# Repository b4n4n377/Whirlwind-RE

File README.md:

# Whirlwind-RE
Clone / Reverse Engineering of the open source 'Whirlwind - PC to JAMMA Arcade Cabinet Interface'
- see https://www.instructables.com/Whirlwind-PC-to-JAMMA-Arcade-Cabinet-Interface/
- see https://github.com/baritonomarchetto/Whirlwind

We encountered a problem where too little voltage reached the video amp due to the voltage divider at pin 1 of the RPI2040 used for sync control.

To address this, we implemented a different sync circuit.

This is one of our very first designs. Ideas for further optimizations are very welcome.

***Shoutouts to** the arcade communities from **Arcade Zone** (https://forum.arcade-zone.de/index.php) and **Groovy Arcade** (https://gitlab.com/groovyarcade/support/-/wikis/home)*

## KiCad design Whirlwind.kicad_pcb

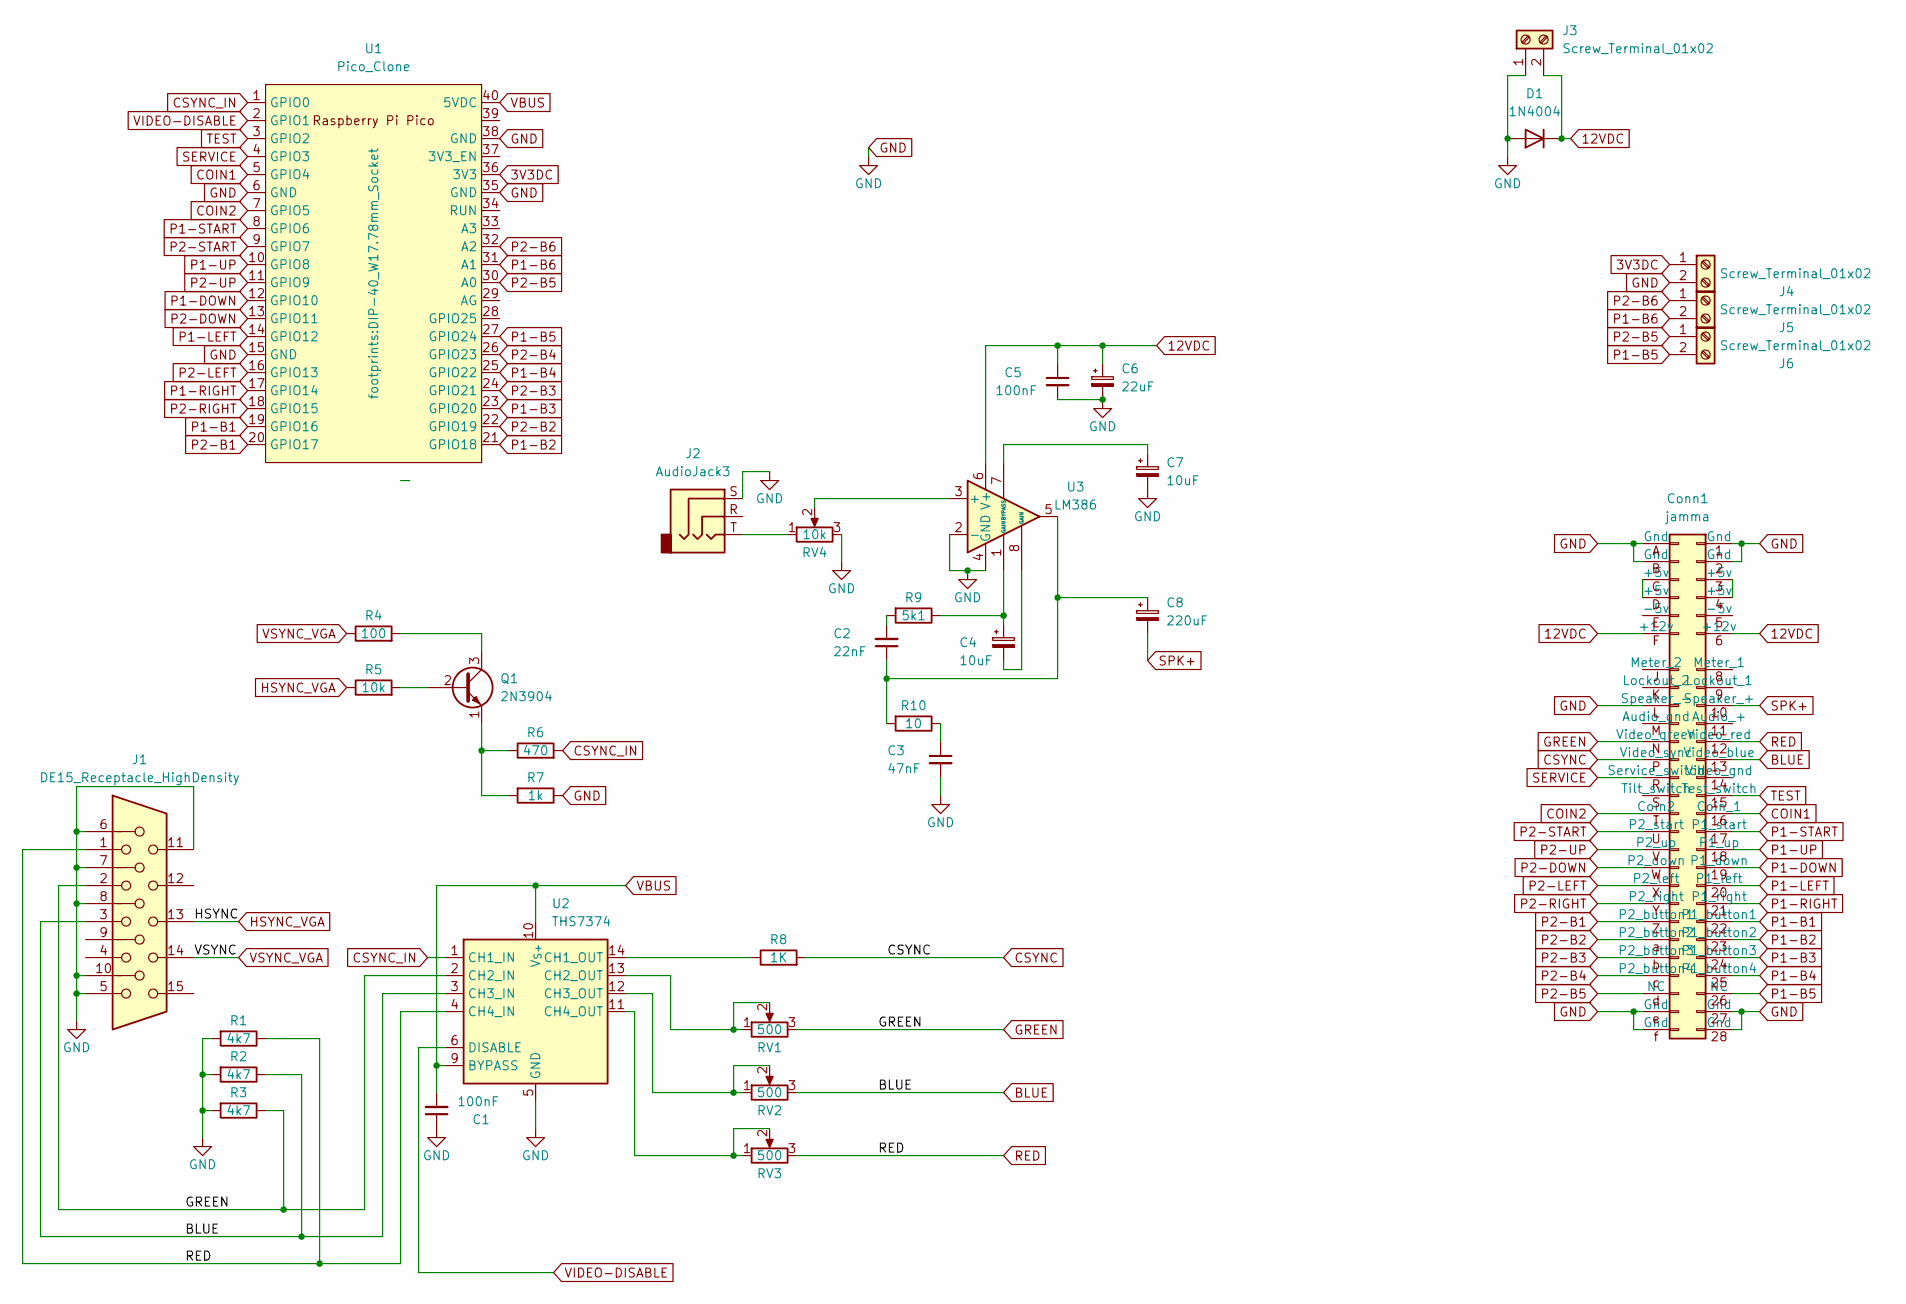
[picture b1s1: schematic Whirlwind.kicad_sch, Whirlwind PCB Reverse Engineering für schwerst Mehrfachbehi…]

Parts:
C1, C5: 100nF; C_Rect_L7.0mm_W2.0mm_P5.00mm
C2: 22nF; C_Rect_L7.0mm_W2.0mm_P5.00mm
C3: 47nF; C_Rect_L7.0mm_W2.0mm_P5.00mm
C4, C7: 10uF; C_Radial_D5.0mm_H11.0mm_P2.00mm
C6: 22uF; C_Radial_D6.3mm_H11.0mm_P2.50mm
C8: 220uF; C_Radial_D6.3mm_H11.0mm_P2.50mm
Conn1: jamma; JAMMA-56
D1: 1N4004; D_DO-41_SOD81_P10.16mm_Horizontal
J1: DE15_Receptacle_HighDensity; DSUB-15-HD_Female_Horizontal_P2.29x1.98mm_EdgePinOffset3.03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
J2: AudioJack3; Jack_3.5mm_CUI_SJ1-3523N_Horizontal
J3, J4, J5, J6: Screw_Terminal_01x02; TerminalBlock_Phoenix_PT-1,5-2-5.0-H_1x02_P5.00mm_Horizontal
Q1: 2N3904; TO-92_Inline
R1, R2, R3: 4k7; R_Axial_DIN0207_L6.3mm_D2.5mm_P10.16mm_Horizontal
R4: 100; R_Axial_DIN0207_L6.3mm_D2.5mm_P10.16mm_Horizontal
R5: 10k; R_Axial_DIN0207_L6.3mm_D2.5mm_P10.16mm_Horizontal
R6: 470; R_Axial_DIN0207_L6.3mm_D2.5mm_P10.16mm_Horizontal
R7: 1k; R_Axial_DIN0207_L6.3mm_D2.5mm_P10.16mm_Horizontal
R8: 1K; R_Axial_DIN0207_L6.3mm_D2.5mm_P10.16mm_Horizontal
R9: 5k1; R_Axial_DIN0207_L6.3mm_D2.5mm_P10.16mm_Horizontal
R10: 10; R_Axial_DIN0207_L6.3mm_D2.5mm_P10.16mm_Horizontal
RV1, RV2, RV3: 500; Potentiometer_Bourns_3386P_Vertical
RV4: 10k; Potentiometer_Bourns_3386P_Vertical
U1: Pico_Clone; DIP-40_W17.78mm_Socket
U2: THS7374; TSSOP-14_4.4x5mm_P0.65mm
U3: LM386; DIP-8_W7.62mm_Socket_LongPads

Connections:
3V3DC: J4.1, U1.36 (3V3)
12VDC: C5.1, C6.1, Conn1.6 (+12v), Conn1.F (+12v), D1.1 (K), J3.2, U3.6 (V+)
BLUE: Conn1.13 (Video_blue), J1.3, R2.1, RV2.3, U2.3 (CH3_IN)
COIN1: Conn1.16 (Coin_1), U1.5 (GPIO4)
COIN2: Conn1.T (Coin2), U1.7 (GPIO5)
CSYNC: Conn1.P (Video_sync), R8.2
CSYNC_IN: R6.2, U1.1 (GPIO0), U2.1 (CH1_IN)
GND: C1.1, C3.2, C5.2, C6.2, C7.2, Conn1.1 (Gnd), Conn1.2 (Gnd), Conn1.27 (Gnd), Conn1.28 (Gnd), Conn1.A (Gnd), Conn1.B (Gnd), Conn1.L (Speaker_-), Conn1.e (Gnd), Conn1.f (Gnd), D1.2 (A), J1.5, J1.6, J1.7, J1.8, J1.10, J1.11, J2.S, J3.1, J4.2, R1.2, R2.2, R3.2, R7.1, RV4.3, U1.6 (GND), U1.15 (GND), U1.35 (GND), U1.38 (GND), U2.5 (GND), U3.2 (-), U3.4 (GND)
GREEN: Conn1.N (Video_green), J1.2, R3.1, RV1.3, U2.2 (CH2_IN)
HSYNC_VGA: J1.13, R5.1
unnamed: C2.1, C8.1, R10.2, U3.5
unnamed: C2.2, R9.2
unnamed: C3.1, R10.1
unnamed: C4.1, R9.1, U3.1 (GAIN)
unnamed: C4.2, U3.8 (GAIN)
unnamed: Conn1.3 (+5v), Conn1.4 (+5v)
unnamed: Conn1.C (+5v), Conn1.D (+5v)
unnamed: J2.T, RV4.1
unnamed: Q1.2 (B), R5.2
unnamed: Q1.3 (C), R4.2
unnamed: Q1.1 (E), R6.1, R7.2
unnamed: R8.1, U2.14 (CH1_OUT)
unnamed: RV1.1, RV1.2, U2.13 (CH2_OUT)
unnamed: RV2.1, RV2.2, U2.12 (CH3_OUT)
unnamed: RV3.1, RV3.2, U2.11 (CH4_OUT)
unnamed: RV4.2, U3.3 (+)
unnamed: C7.1, U3.7 (BYPASS)
P1-B1: Conn1.22 (P1_button1), U1.19 (GPIO16)
P1-B2: Conn1.23 (P1_button2), U1.21 (GPIO18)
P1-B3: Conn1.24 (P1_button3), U1.23 (GPIO20)
P1-B4: Conn1.25 (P1_button4), U1.25 (GPIO22)
P1-B5: Conn1.26 (NC), J6.2, U1.27 (GPIO24)
P1-B6: J5.2, U1.31 (A1)
P1-DOWN: Conn1.19 (P1_down), U1.12 (GPIO10)
P1-LEFT: Conn1.20 (P1_left), U1.14 (GPIO12)
P1-RIGHT: Conn1.21 (P1_right), U1.17 (GPIO14)
P1-START: Conn1.17 (P1_start), U1.8 (GPIO6)
P1-UP: Conn1.18 (P1_up), U1.10 (GPIO8)
P2-B1: Conn1.Z (P2_button1), U1.20 (GPIO17)
P2-B2: Conn1.a (P2_button2), U1.22 (GPIO19)
P2-B3: Conn1.b (P2_button3), U1.24 (GPIO21)
P2-B4: Conn1.c (P2_button4), U1.26 (GPIO23)
P2-B5: Conn1.d (NC), J6.1, U1.30 (A0)
P2-B6: J5.1, U1.32 (A2)
P2-DOWN: Conn1.W (P2_down), U1.13 (GPIO11)
P2-LEFT: Conn1.X (P2_left), U1.16 (GPIO13)
P2-RIGHT: Conn1.Y (P2_right), U1.18 (GPIO15)
P2-START: Conn1.U (P2_start), U1.9 (GPIO7)
P2-UP: Conn1.V (P2_up), U1.11 (GPIO9)
RED: Conn1.12 (Video_red), J1.1, R1.1, RV3.3, U2.4 (CH4_IN)
SERVICE: Conn1.R (Service_switch), U1.4 (GPIO3)
SPK+: C8.2, Conn1.10 (Speaker_+)
TEST: Conn1.15 (Test_switch), U1.3 (GPIO2)
VBUS: C1.2, U1.40 (5VDC), U2.9 (BYPASS), U2.10 (V_{S+})
VIDEO-DISABLE: U1.2 (GPIO1), U2.6 (DISABLE)
VSYNC_VGA: J1.14, R4.1

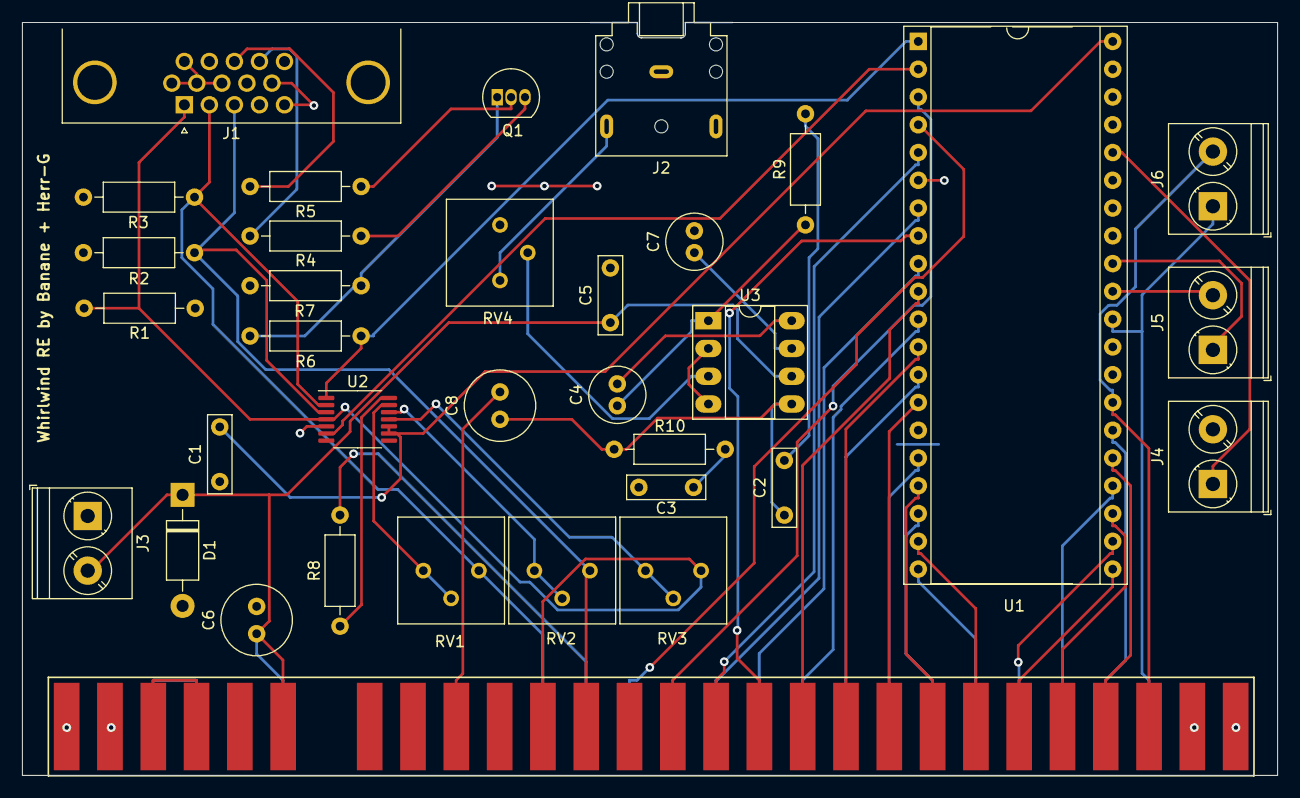
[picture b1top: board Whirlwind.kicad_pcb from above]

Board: 2 copper layers, 114.8 x 68.9 mm, 34 parts (0 on the bottom side), 56 nets.

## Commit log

2024-04-18 Initial
2024-04-20 Mandatory Credits
